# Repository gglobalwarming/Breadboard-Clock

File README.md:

# Breadboard-Clock
Files generated while building Ben Eater's breadboard clock following his YouTube series. https://www.youtube.com/watch?v=3XDH-fZKnQk&t=880s

Write-up reviewing how a few key elements of the clock work: In progress  
Schematics: Complete, need to verify that I didn't mess anything up  
Build clock: Have Ben's kit, but have not built it 
Footprints: Need to check capacitor footprints, find/make proper button footprints  
Board design: Not started.  
Build clock on PCB: I may or may not do this.  
  
Note: I have not yet built the clock so my schematics are untested. Use blindly at your own risk. Please submit an issue if you find any errors!

Attached footprints downloaded from Mouser entries for the relevant chips. https://eater.net/clock

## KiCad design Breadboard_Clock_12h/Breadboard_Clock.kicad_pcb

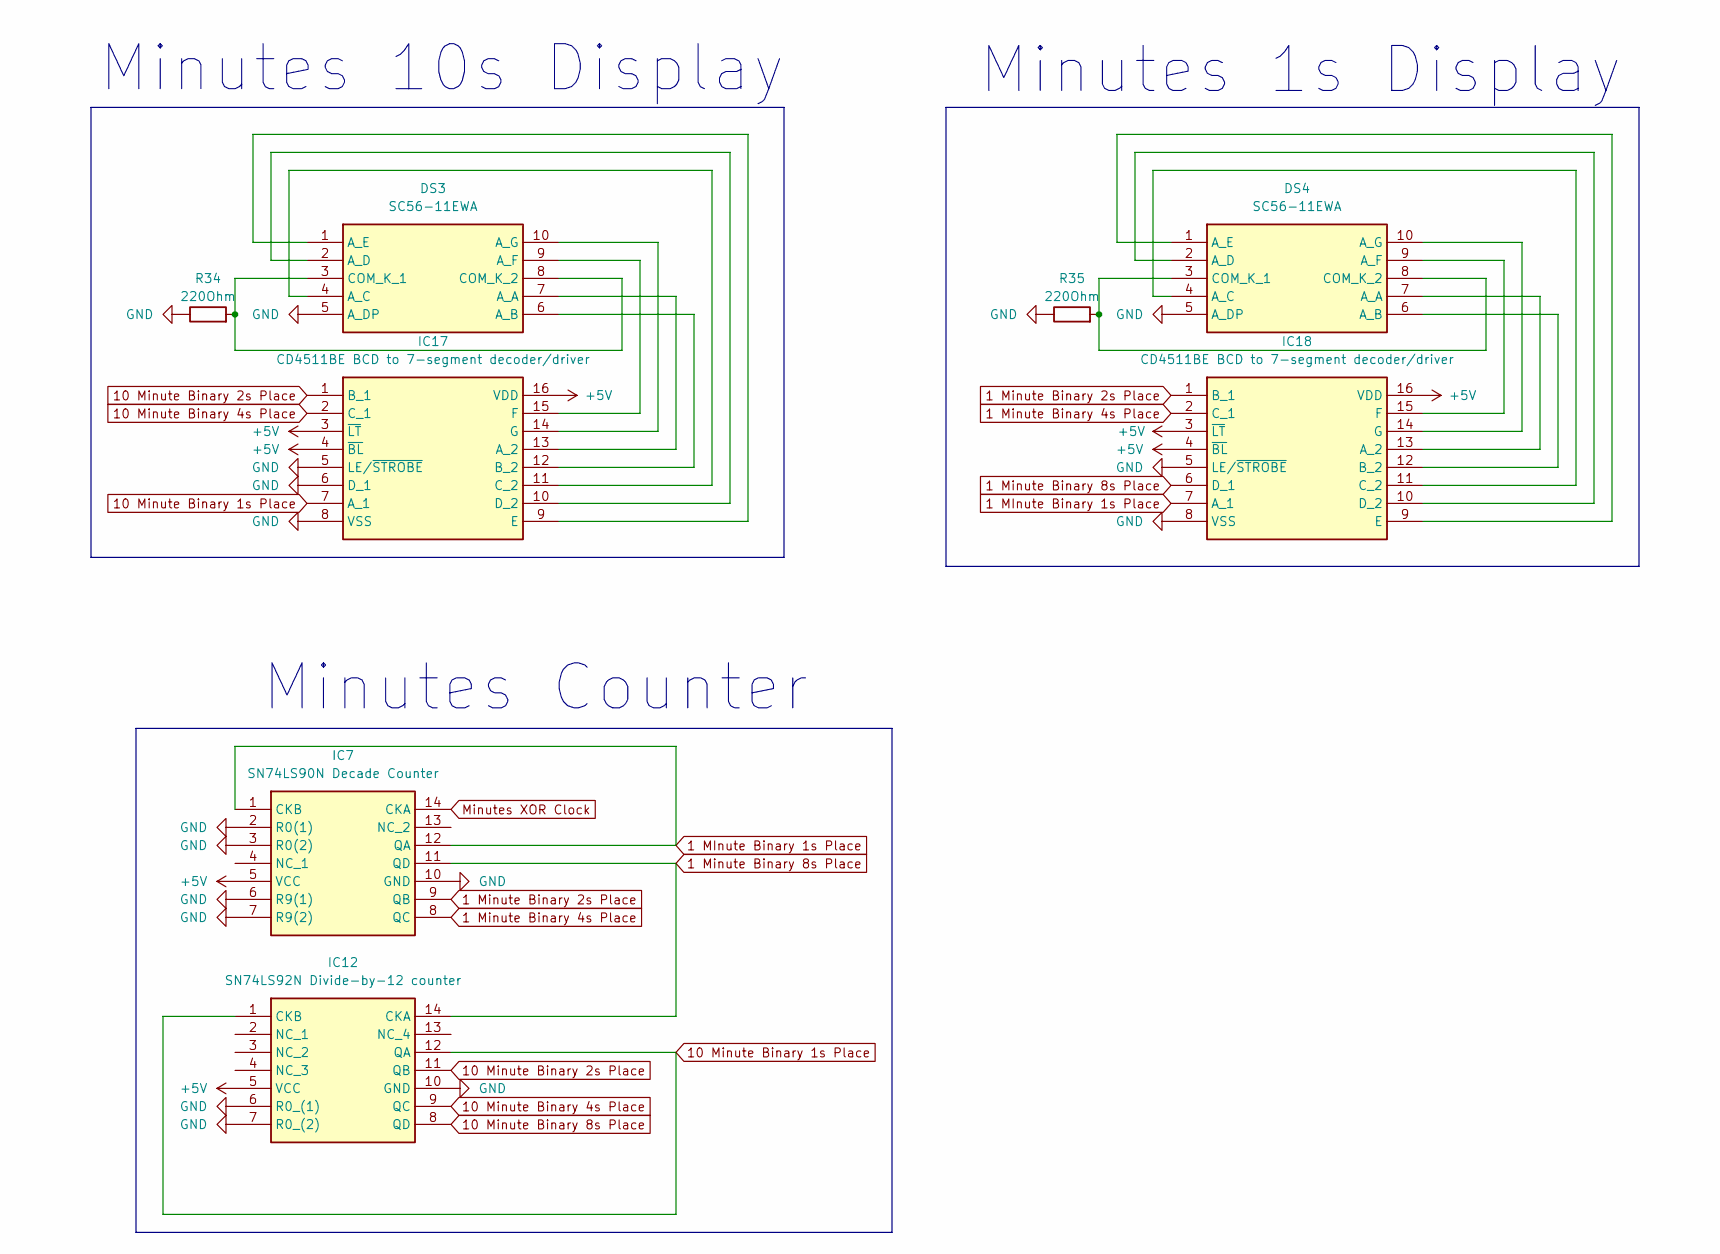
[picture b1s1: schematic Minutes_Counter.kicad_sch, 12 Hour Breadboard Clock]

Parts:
DS3, DS4: SC56-11EWA; DIPS1524W75P254L1270H825Q10N; Mouser Part Number 604-SC56-11EWA
IC7: SN74LS90N Decade Counter; DIP794W53P254L1930H508Q14N; Mouser Part Number 595-SN74LS90N
IC12: SN74LS92N Divide-by-12 counter; DIP794W53P254L1930H508Q14N; Mouser Part Number 595-SN74LS92N
IC17, IC18: CD4511BE BCD to 7-segment decoder/driver; DIP794W53P254L1930H508Q16N; Mouser Part Number 595-CD4511BE
R34, R35: 220Ohm; R_Axial_DIN0207_L6.3mm_D2.5mm_P10.16mm_Horizontal

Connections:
1 MInute Binary 1s Place: IC7.1 (CKB), IC7.12 (QA), IC18.7 (A_1)
1 Minute Binary 2s Place: IC7.9 (QB), IC18.1 (B_1)
1 Minute Binary 4s Place: IC7.8 (QC), IC18.2 (C_1)
1 Minute Binary 8s Place: IC7.11 (QD), IC12.14 (CKA), IC18.6 (D_1)
10 Minute Binary 1s Place: IC12.1 (CKB), IC12.12 (QA), IC17.7 (A_1)
10 Minute Binary 2s Place: IC12.11 (QB), IC17.1 (B_1)
10 Minute Binary 4s Place: IC12.9 (QC), IC17.2 (C_1); also elsewhere on the board
10 Minute Binary 8s Place: IC12.8 (QD)
+5V: IC7.5 (VCC), IC12.5 (VCC), IC17.3 (~LT), IC17.4 (~BL), IC17.16 (VDD), IC18.3 (~LT), IC18.4 (~BL), IC18.16 (VDD); also elsewhere on the board
GND: DS3.5 (A_DP), DS4.5 (A_DP), IC7.2 (R0(1)), IC7.3 (R0(2)), IC7.6 (R9(1)), IC7.7 (R9(2)), IC7.10 (GND), IC12.6 (R0_(1)), IC12.7 (R0_(2)), IC12.10 (GND), IC17.5 (LE/~STROBE), IC17.6 (D_1), IC17.8 (VSS), IC18.5 (LE/~STROBE), IC18.8 (VSS), R34.1, R35.1; also elsewhere on the board
Minutes XOR Clock: IC7.14 (CKA); also elsewhere on the board
unnamed: DS3.7 (A_A), IC17.13 (A_2)
unnamed: DS3.6 (A_B), IC17.12 (B_2)
unnamed: DS3.4 (A_C), IC17.11 (C_2)
unnamed: DS3.2 (A_D), IC17.10 (D_2)
unnamed: DS3.1 (A_E), IC17.9 (E)
unnamed: DS3.9 (A_F), IC17.15 (F)
unnamed: DS3.10 (A_G), IC17.14 (G)
unnamed: DS3.3 (COM_K_1), DS3.8 (COM_K_2), R34.2
unnamed: DS4.7 (A_A), IC18.13 (A_2)
unnamed: DS4.6 (A_B), IC18.12 (B_2)
unnamed: DS4.4 (A_C), IC18.11 (C_2)
unnamed: DS4.2 (A_D), IC18.10 (D_2)
unnamed: DS4.1 (A_E), IC18.9 (E)
unnamed: DS4.9 (A_F), IC18.15 (F)
unnamed: DS4.10 (A_G), IC18.14 (G)
unnamed: DS4.3 (COM_K_1), DS4.8 (COM_K_2), R35.2

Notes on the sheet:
Minutes 10s Display
Minutes 1s Display
Minutes Counter

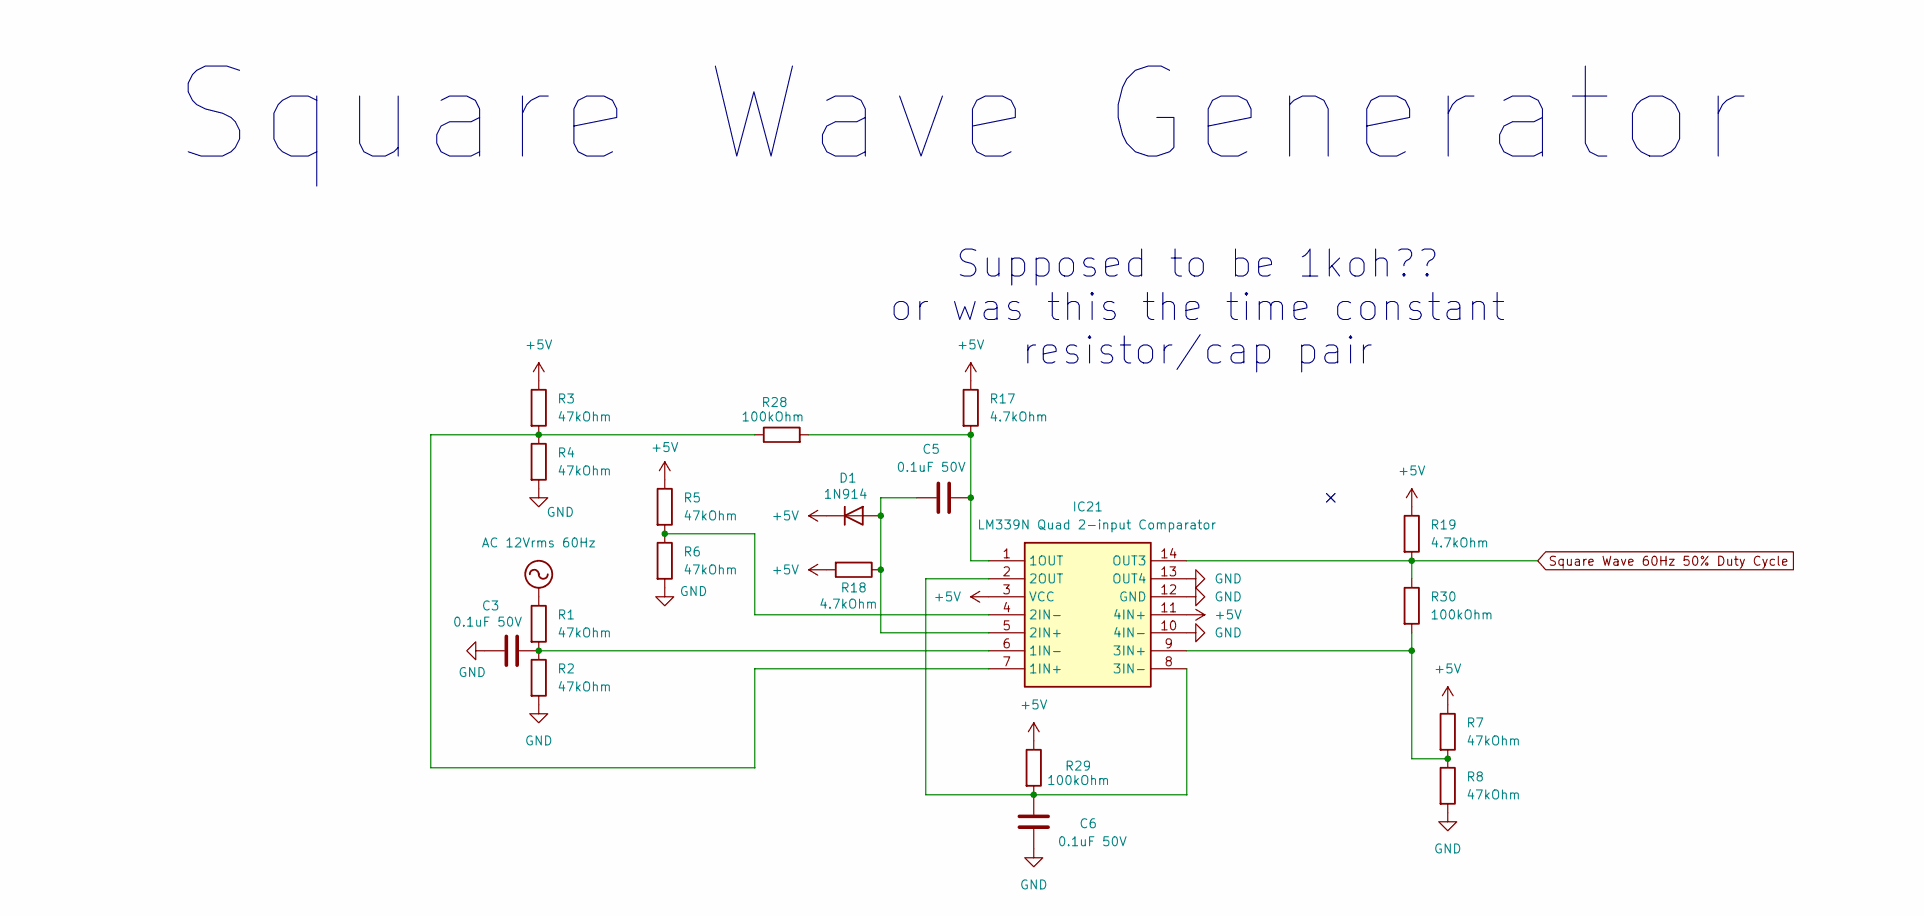
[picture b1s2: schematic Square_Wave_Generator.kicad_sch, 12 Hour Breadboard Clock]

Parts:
C3, C5, C6: 0.1uF 50V; C_Rect_L4.0mm_W2.5mm_P2.50mm
D1: 1N914; D_DO-35_SOD27_P7.62mm_Horizontal
IC21: LM339N Quad 2-input Comparator; DIP794W53P254L1930H508Q14N; Mouser Part Number 595-LM339N
R1, R2, R3, R4, R5, R6, R7, R8: 47kOhm; R_Axial_DIN0207_L6.3mm_D2.5mm_P10.16mm_Horizontal
R17, R18, R19: 4.7kOhm; R_Axial_DIN0207_L6.3mm_D2.5mm_P10.16mm_Horizontal
R28, R29, R30: 100kOhm; R_Axial_DIN0207_L6.3mm_D2.5mm_P10.16mm_Horizontal

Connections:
+5V: D1.1 (K), IC21.3 (VCC), IC21.11 (4IN+), R3.1, R5.1, R7.1, R17.1, R18.2, R19.1, R29.1; also elsewhere on the board
AC 12Vrms 60Hz: R1.1; also elsewhere on the board
GND: C3.2, C6.2, IC21.10 (4IN-), IC21.12 (GND), IC21.13 (OUT4), R2.2, R4.2, R6.2, R8.2; also elsewhere on the board
unnamed: C5.2, D1.2 (A), IC21.5 (2IN+), R18.1
unnamed: IC21.7 (1IN+), R3.2, R4.1, R28.1
unnamed: C3.1, IC21.6 (1IN-), R1.2, R2.1
unnamed: C5.1, IC21.1 (1OUT), R17.2, R28.2
unnamed: IC21.4 (2IN-), R5.2, R6.1
unnamed: C6.1, IC21.2 (2OUT), IC21.8 (3IN-), R29.2
unnamed: IC21.9 (3IN+), R7.2, R8.1, R30.2
Square Wave 60Hz 50% Duty Cycle: IC21.14 (OUT3), R19.2, R30.1; also elsewhere on the board

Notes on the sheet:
Square Wave Generator
Supposed to be 1koh?? or was this the time constant resistor/cap pair

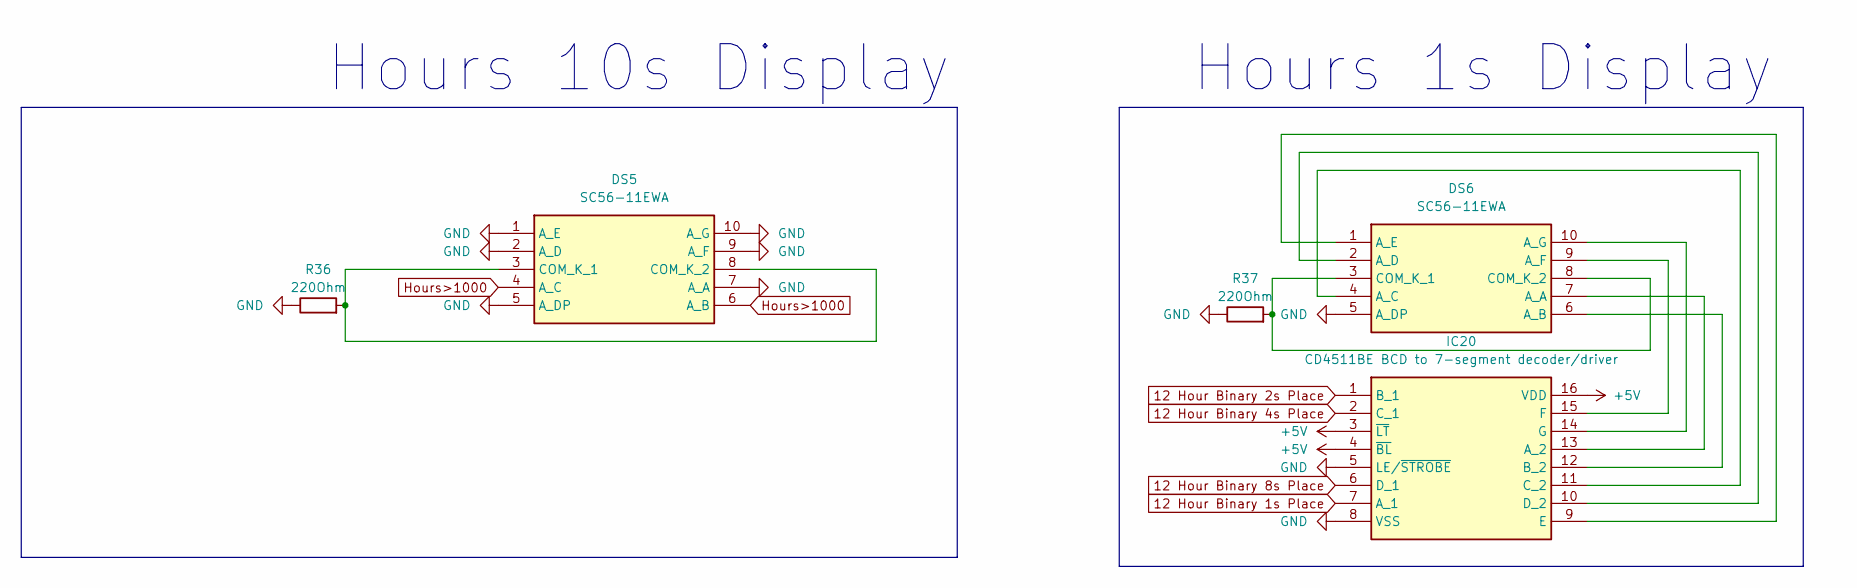
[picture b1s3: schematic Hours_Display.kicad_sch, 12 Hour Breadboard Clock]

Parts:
DS5, DS6: SC56-11EWA; DIPS1524W75P254L1270H825Q10N; Mouser Part Number 604-SC56-11EWA
IC20: CD4511BE BCD to 7-segment decoder/driver; DIP794W53P254L1930H508Q16N; Mouser Part Number 595-CD4511BE
R36, R37: 220Ohm; R_Axial_DIN0207_L6.3mm_D2.5mm_P10.16mm_Horizontal

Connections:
12 Hour Binary 1s Place: IC20.7 (A_1); also elsewhere on the board
12 Hour Binary 2s Place: IC20.1 (B_1); also elsewhere on the board
12 Hour Binary 4s Place: IC20.2 (C_1); also elsewhere on the board
12 Hour Binary 8s Place: IC20.6 (D_1); also elsewhere on the board
+5V: IC20.3 (~LT), IC20.4 (~BL), IC20.16 (VDD); also elsewhere on the board
GND: DS5.1 (A_E), DS5.2 (A_D), DS5.5 (A_DP), DS5.7 (A_A), DS5.9 (A_F), DS5.10 (A_G), DS6.5 (A_DP), IC20.5 (LE/~STROBE), IC20.8 (VSS), R36.1, R37.1; also elsewhere on the board
Hours>1000: DS5.4 (A_C), DS5.6 (A_B); also elsewhere on the board
unnamed: DS5.3 (COM_K_1), DS5.8 (COM_K_2), R36.2
unnamed: DS6.7 (A_A), IC20.13 (A_2)
unnamed: DS6.6 (A_B), IC20.12 (B_2)
unnamed: DS6.4 (A_C), IC20.11 (C_2)
unnamed: DS6.2 (A_D), IC20.10 (D_2)
unnamed: DS6.1 (A_E), IC20.9 (E)
unnamed: DS6.9 (A_F), IC20.15 (F)
unnamed: DS6.10 (A_G), IC20.14 (G)
unnamed: DS6.3 (COM_K_1), DS6.8 (COM_K_2), R37.2

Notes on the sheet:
Hours 10s Display
Hours 1s Display

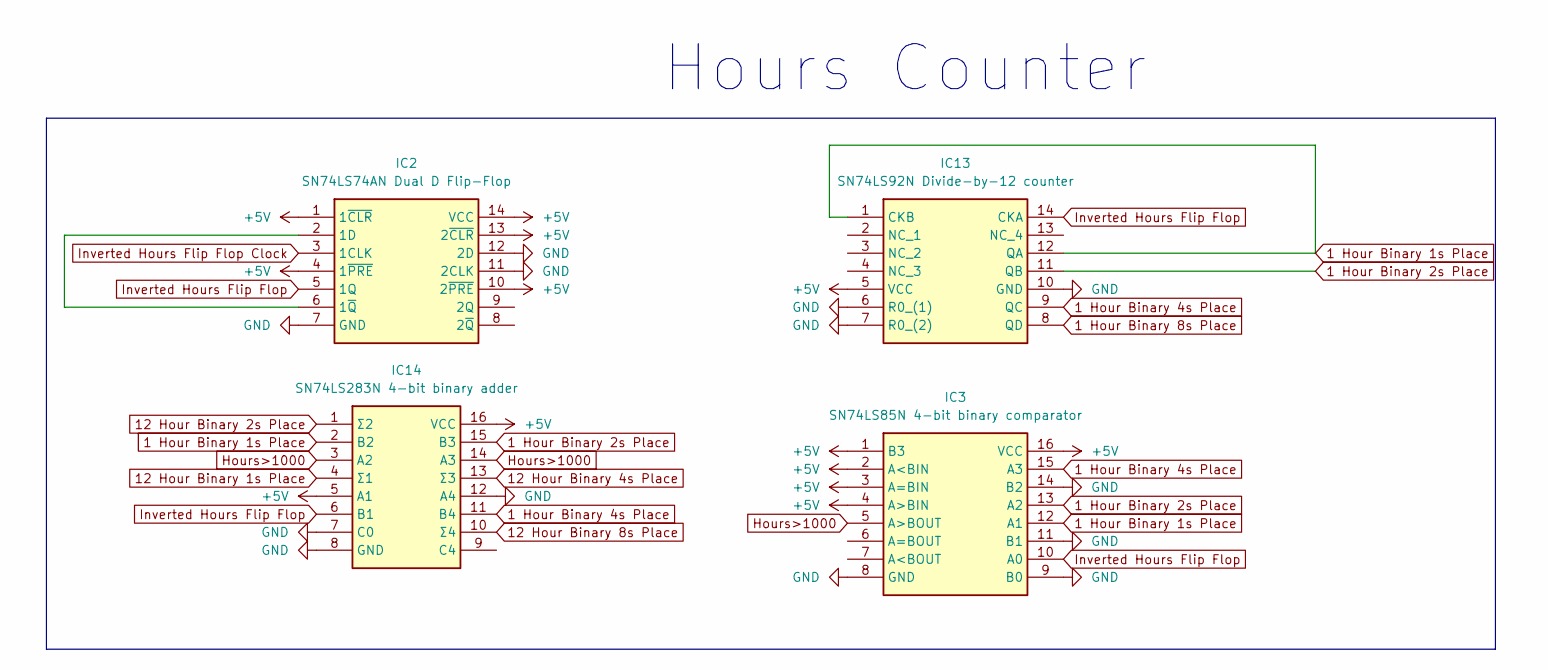
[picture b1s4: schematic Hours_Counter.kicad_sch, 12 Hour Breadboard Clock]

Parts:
IC2: SN74LS74AN Dual D Flip-Flop; DIP794W53P254L1930H508Q14N; Mouser Part Number 595-SN74LS74AN
IC3: SN74LS85N 4-bit binary comparator; DIP794W53P254L1930H508Q16N; Mouser Part Number 595-SN74LS85N
IC13: SN74LS92N Divide-by-12 counter; DIP794W53P254L1930H508Q14N; Mouser Part Number 595-SN74LS92N
IC14: SN74LS283N 4-bit binary adder; DIP794W53P254L1930H508Q16N; Mouser Part Number 595-SN74LS283N

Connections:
1 Hour Binary 1s Place: IC3.12 (A1), IC13.1 (CKB), IC13.12 (QA), IC14.2 (B2)
1 Hour Binary 2s Place: IC3.13 (A2), IC13.11 (QB), IC14.15 (B3)
1 Hour Binary 4s Place: IC3.15 (A3), IC13.9 (QC), IC14.11 (B4)
1 Hour Binary 8s Place: IC13.8 (QD)
12 Hour Binary 1s Place: IC14.4 (Σ1); also elsewhere on the board
12 Hour Binary 2s Place: IC14.1 (Σ2); also elsewhere on the board
12 Hour Binary 4s Place: IC14.13 (Σ3); also elsewhere on the board
12 Hour Binary 8s Place: IC14.10 (Σ4); also elsewhere on the board
+5V: IC2.1 (1~CLR), IC2.4 (1~PRE), IC2.10 (2~PRE), IC2.13 (2~CLR), IC2.14 (VCC), IC3.1 (B3), IC3.2 (A<BIN), IC3.3 (A=BIN), IC3.4 (A>BIN), IC3.16 (VCC), IC13.5 (VCC), IC14.5 (A1), IC14.16 (VCC); also elsewhere on the board
GND: IC2.7 (GND), IC2.11 (2CLK), IC2.12 (2D), IC3.8 (GND), IC3.9 (B0), IC3.11 (B1), IC3.14 (B2), IC13.6 (R0_(1)), IC13.7 (R0_(2)), IC13.10 (GND), IC14.7 (C0), IC14.8 (GND), IC14.12 (A4); also elsewhere on the board
Hours>1000: IC3.5 (A>BOUT), IC14.3 (A2), IC14.14 (A3); also elsewhere on the board
Inverted Hours Flip Flop: IC2.5 (1Q), IC3.10 (A0), IC13.14 (CKA), IC14.6 (B1)
Inverted Hours Flip Flop Clock: IC2.3 (1CLK); also elsewhere on the board
unnamed: IC2.2 (1D), IC2.6 (1~Q)

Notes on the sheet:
Hours Counter

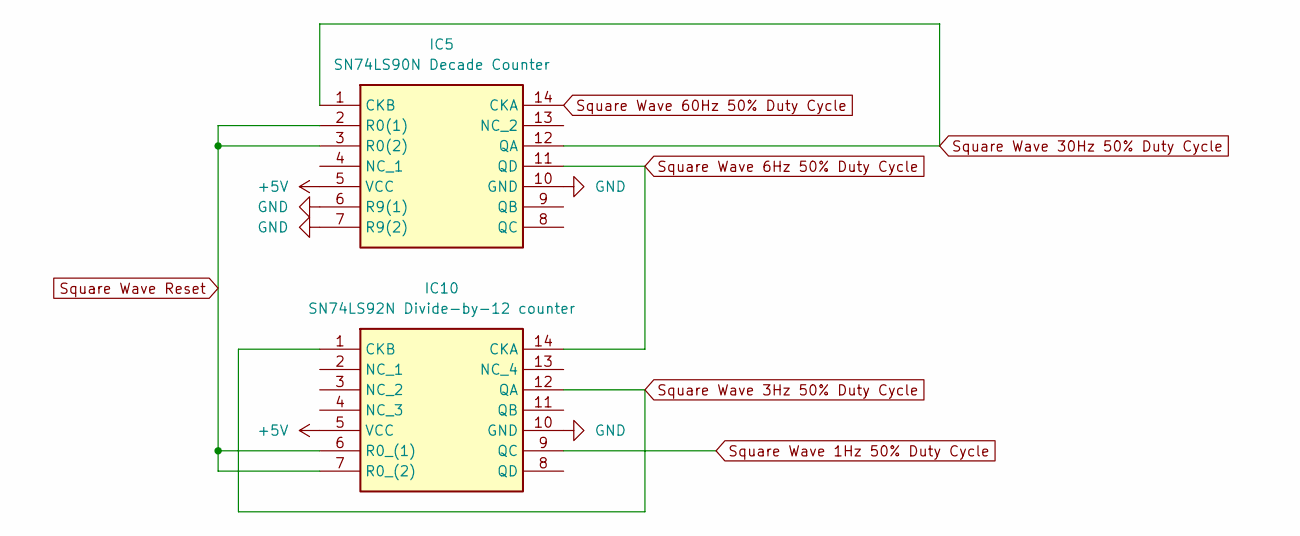
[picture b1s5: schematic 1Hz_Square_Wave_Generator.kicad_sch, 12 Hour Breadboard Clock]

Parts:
IC5: SN74LS90N Decade Counter; DIP794W53P254L1930H508Q14N; Mouser Part Number 595-SN74LS90N
IC10: SN74LS92N Divide-by-12 counter; DIP794W53P254L1930H508Q14N; Mouser Part Number 595-SN74LS92N

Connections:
+5V: IC5.5 (VCC), IC10.5 (VCC); also elsewhere on the board
GND: IC5.6 (R9(1)), IC5.7 (R9(2)), IC5.10 (GND), IC10.10 (GND); also elsewhere on the board
Seconds Reset: IC5.2 (R0(1)), IC5.3 (R0(2)), IC10.6 (R0_(1)), IC10.7 (R0_(2)); also elsewhere on the board
Square Wave 1Hz 50% Duty Cycle: IC10.9 (QC); also elsewhere on the board
Square Wave 3Hz 50% Duty Cycle: IC10.1 (CKB), IC10.12 (QA); also elsewhere on the board
Square Wave 6Hz 50% Duty Cycle: IC5.11 (QD), IC10.14 (CKA)
Square Wave 30Hz 50% Duty Cycle: IC5.1 (CKB), IC5.12 (QA)
Square Wave 60Hz 50% Duty Cycle: IC5.14 (CKA); also elsewhere on the board

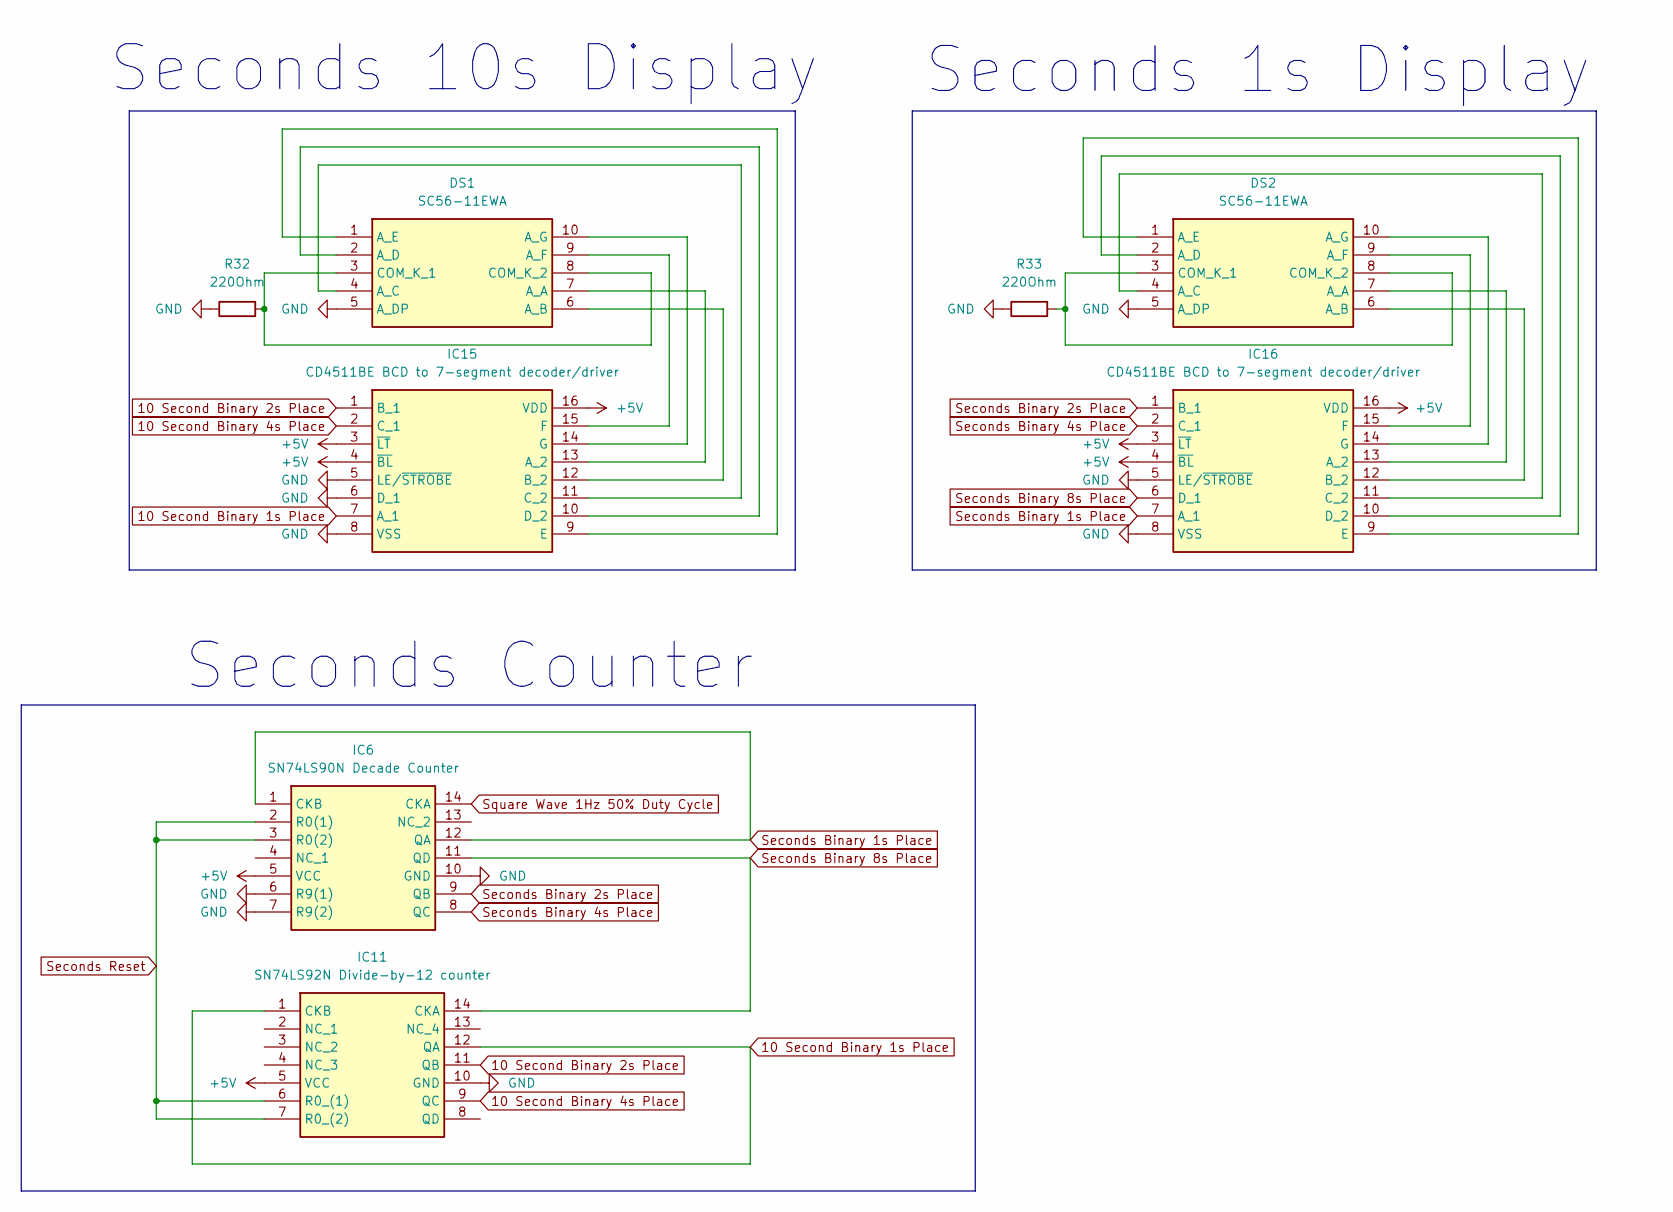
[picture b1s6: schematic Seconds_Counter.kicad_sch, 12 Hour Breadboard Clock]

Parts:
DS1, DS2: SC56-11EWA; DIPS1524W75P254L1270H825Q10N; Mouser Part Number 604-SC56-11EWA
IC6: SN74LS90N Decade Counter; DIP794W53P254L1930H508Q14N; Mouser Part Number 595-SN74LS90N
IC11: SN74LS92N Divide-by-12 counter; DIP794W53P254L1930H508Q14N; Mouser Part Number 595-SN74LS92N
IC15, IC16: CD4511BE BCD to 7-segment decoder/driver; DIP794W53P254L1930H508Q16N; Mouser Part Number 595-CD4511BE
R32, R33: 220Ohm; R_Axial_DIN0207_L6.3mm_D2.5mm_P10.16mm_Horizontal

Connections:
10 Second Binary 1s Place: IC11.1 (CKB), IC11.12 (QA), IC15.7 (A_1)
10 Second Binary 2s Place: IC11.11 (QB), IC15.1 (B_1)
10 Second Binary 4s Place: IC11.9 (QC), IC15.2 (C_1); also elsewhere on the board
+5V: IC6.5 (VCC), IC11.5 (VCC), IC15.3 (~LT), IC15.4 (~BL), IC15.16 (VDD), IC16.3 (~LT), IC16.4 (~BL), IC16.16 (VDD); also elsewhere on the board
GND: DS1.5 (A_DP), DS2.5 (A_DP), IC6.6 (R9(1)), IC6.7 (R9(2)), IC6.10 (GND), IC11.10 (GND), IC15.5 (LE/~STROBE), IC15.6 (D_1), IC15.8 (VSS), IC16.5 (LE/~STROBE), IC16.8 (VSS), R32.1, R33.1; also elsewhere on the board
unnamed: DS1.7 (A_A), IC15.13 (A_2)
unnamed: DS1.6 (A_B), IC15.12 (B_2)
unnamed: DS1.4 (A_C), IC15.11 (C_2)
unnamed: DS1.2 (A_D), IC15.10 (D_2)
unnamed: DS1.1 (A_E), IC15.9 (E)
unnamed: DS1.9 (A_F), IC15.15 (F)
unnamed: DS1.10 (A_G), IC15.14 (G)
unnamed: DS1.3 (COM_K_1), DS1.8 (COM_K_2), R32.2
unnamed: DS2.7 (A_A), IC16.13 (A_2)
unnamed: DS2.6 (A_B), IC16.12 (B_2)
unnamed: DS2.4 (A_C), IC16.11 (C_2)
unnamed: DS2.2 (A_D), IC16.10 (D_2)
unnamed: DS2.1 (A_E), IC16.9 (E)
unnamed: DS2.9 (A_F), IC16.15 (F)
unnamed: DS2.10 (A_G), IC16.14 (G)
unnamed: DS2.3 (COM_K_1), DS2.8 (COM_K_2), R33.2
Seconds Binary 1s Place: IC6.1 (CKB), IC6.12 (QA), IC16.7 (A_1)
Seconds Binary 2s Place: IC6.9 (QB), IC16.1 (B_1)
Seconds Binary 4s Place: IC6.8 (QC), IC16.2 (C_1)
Seconds Binary 8s Place: IC6.11 (QD), IC11.14 (CKA), IC16.6 (D_1)
Seconds Reset: IC6.2 (R0(1)), IC6.3 (R0(2)), IC11.6 (R0_(1)), IC11.7 (R0_(2)); also elsewhere on the board
Square Wave 1Hz 50% Duty Cycle: IC6.14 (CKA); also elsewhere on the board

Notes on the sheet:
Seconds 1s Display
Seconds Counter
Seconds 10s Display

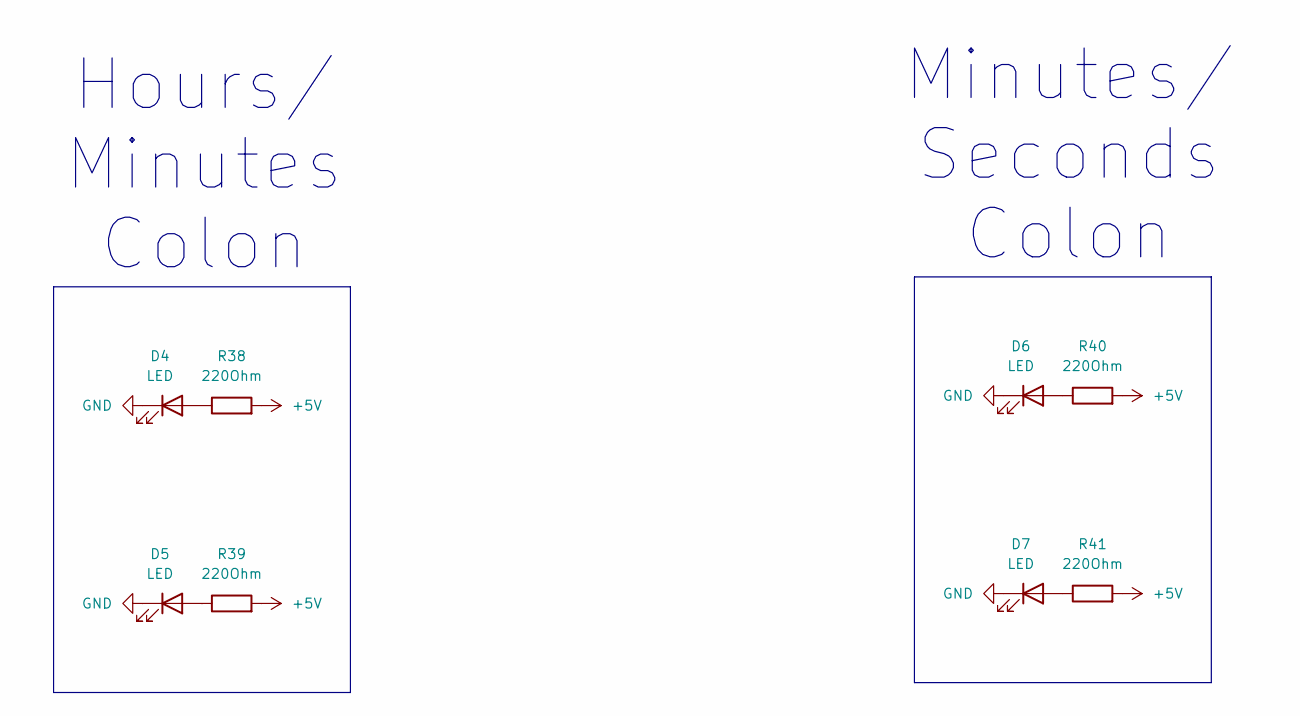
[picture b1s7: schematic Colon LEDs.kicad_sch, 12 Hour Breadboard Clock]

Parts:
D4, D5, D6, D7: LED; LED_D3.0mm
R38, R39, R40, R41: 220Ohm; R_Axial_DIN0207_L6.3mm_D2.5mm_P10.16mm_Horizontal

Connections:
+5V: R38.2, R39.2, R40.2, R41.2; also elsewhere on the board
GND: D4.1 (K), D5.1 (K), D6.1 (K), D7.1 (K); also elsewhere on the board
unnamed: D4.2 (A), R38.1
unnamed: D5.2 (A), R39.1
unnamed: D6.2 (A), R40.1
unnamed: D7.2 (A), R41.1

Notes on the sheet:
Minutes/ Seconds Colon
Hours/ Minutes Colon

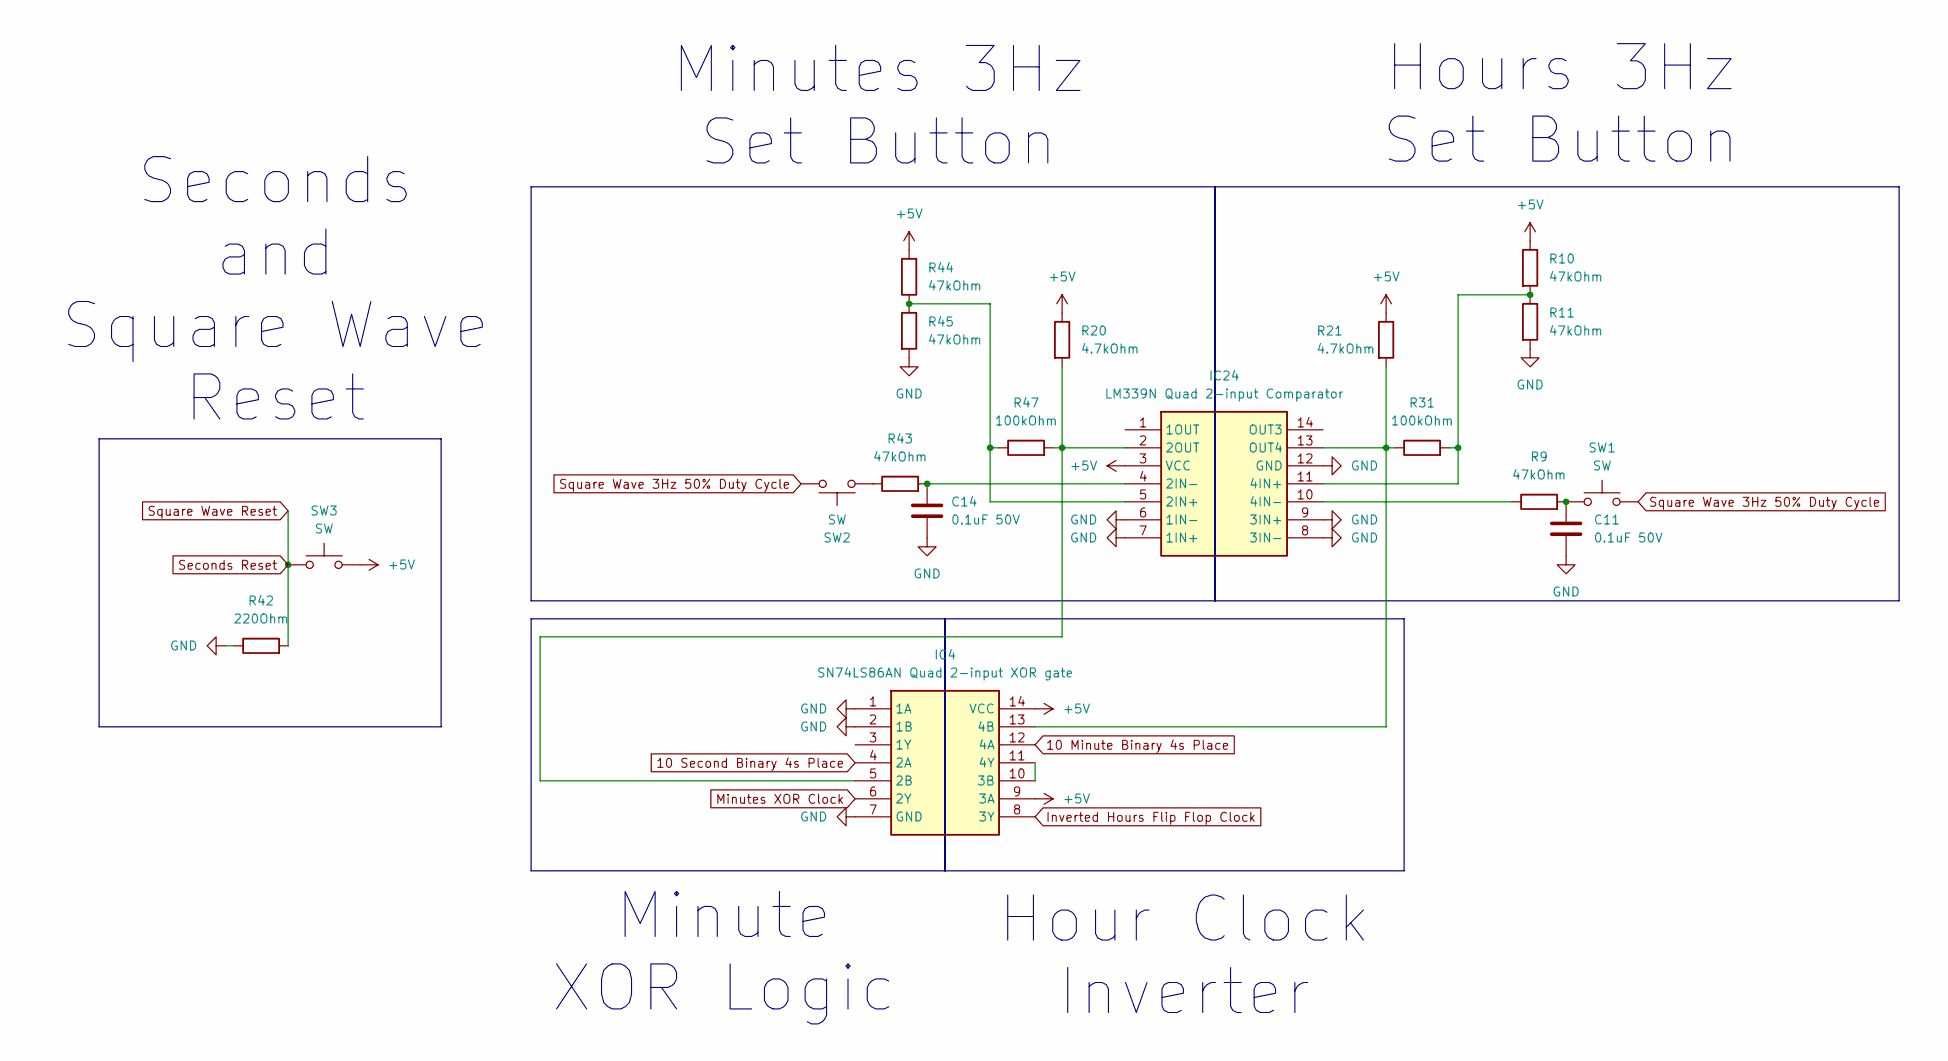
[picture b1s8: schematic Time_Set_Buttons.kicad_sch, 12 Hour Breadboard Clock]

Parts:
C11, C14: 0.1uF 50V; C_Rect_L4.0mm_W2.5mm_P2.50mm
IC4: SN74LS86AN Quad 2-input XOR gate; DIP794W53P254L1930H508Q14N; Mouser Part Number 595-SN74LS86AN
IC24: LM339N Quad 2-input Comparator; DIP794W53P254L1930H508Q14N; Mouser Part Number 595-LM339N
R9, R10, R11, R43, R44, R45: 47kOhm; R_Axial_DIN0207_L6.3mm_D2.5mm_P10.16mm_Horizontal
R20, R21: 4.7kOhm; R_Axial_DIN0207_L6.3mm_D2.5mm_P10.16mm_Horizontal
R31, R47: 100kOhm; R_Axial_DIN0207_L6.3mm_D2.5mm_P10.16mm_Horizontal
R42: 220Ohm; R_Axial_DIN0207_L6.3mm_D2.5mm_P10.16mm_Horizontal
SW1, SW2, SW3: SW; PinHeader_2x01_P2.54mm_Vertical

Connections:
10 Minute Binary 4s Place: IC4.12 (4A); also elsewhere on the board
10 Second Binary 4s Place: IC4.4 (2A); also elsewhere on the board
+5V: IC4.9 (3A), IC4.14 (VCC), IC24.3 (VCC), R10.1, R20.1, R21.1, R44.2, SW3.2; also elsewhere on the board
GND: C11.2, C14.1, IC4.1 (1A), IC4.2 (1B), IC4.7 (GND), IC24.6 (1IN-), IC24.7 (1IN+), IC24.8 (3IN-), IC24.9 (3IN+), IC24.12 (GND), R11.2, R42.1, R45.2; also elsewhere on the board
Inverted Hours Flip Flop Clock: IC4.8 (3Y); also elsewhere on the board
Minutes XOR Clock: IC4.6 (2Y); also elsewhere on the board
unnamed: C11.1, R9.2, SW1.1
unnamed: IC4.10 (3B), IC4.11 (4Y)
unnamed: IC24.5 (2IN+), R44.1, R45.1, R47.1
unnamed: C14.2, IC24.4 (2IN-), R43.2
unnamed: IC4.5 (2B), IC24.2 (2OUT), R20.2, R47.2
unnamed: IC24.11 (4IN+), R10.2, R11.1, R31.2
unnamed: IC24.10 (4IN-), R9.1
unnamed: IC4.13 (4B), IC24.13 (OUT4), R21.2, R31.1
unnamed: R43.1, SW2.1
Seconds Reset: R42.2, SW3.1; also elsewhere on the board
Square Wave 3Hz 50% Duty Cycle: SW1.2, SW2.2; also elsewhere on the board

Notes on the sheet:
Hour Clock Inverter
Seconds and Square Wave Reset
Hours 3Hz Set Button
Minutes 3Hz Set Button
Minute XOR Logic

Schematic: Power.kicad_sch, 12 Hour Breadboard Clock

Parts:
BR1: DB105-BP Bridge rectifier; DB105BP; Mouser Part Number 833-DB105-BP
C1: 10000uF 16V; CP_Radial_D18.0mm_P7.50mm
C2, C4, C7, C8, C9, C10: 0.1uF 50V; C_Rect_L4.0mm_W2.5mm_P2.50mm
IC23: L7805CV; TO255P460X1020X2008-3P; Mouser Part Number 511-L7805CV

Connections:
+5V: C2.1, C7.1, C8.1, C9.1, C10.1, IC23.3 (OUTPUT); also elsewhere on the board
+12V: BR1.1 (+), C1.1, C4.1, IC23.1 (INPUT)
AC 12Vrms 60Hz: BR1.3 (~_1), BR1.4 (~_2); also elsewhere on the board
GND: BR1.2 (-), C1.2, C2.2, C4.2, C7.2, C8.2, C9.2, C10.2, IC23.2 (GROUND); also elsewhere on the board

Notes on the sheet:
12V DC and 5V DC
Extra Power Rail Noise Reduction

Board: 2 copper layers, 81 parts (0 on the bottom side), 97 nets, no tracks yet.
